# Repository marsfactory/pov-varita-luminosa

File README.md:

# pov-varita-luminosa
persistence of vision withs leds stick

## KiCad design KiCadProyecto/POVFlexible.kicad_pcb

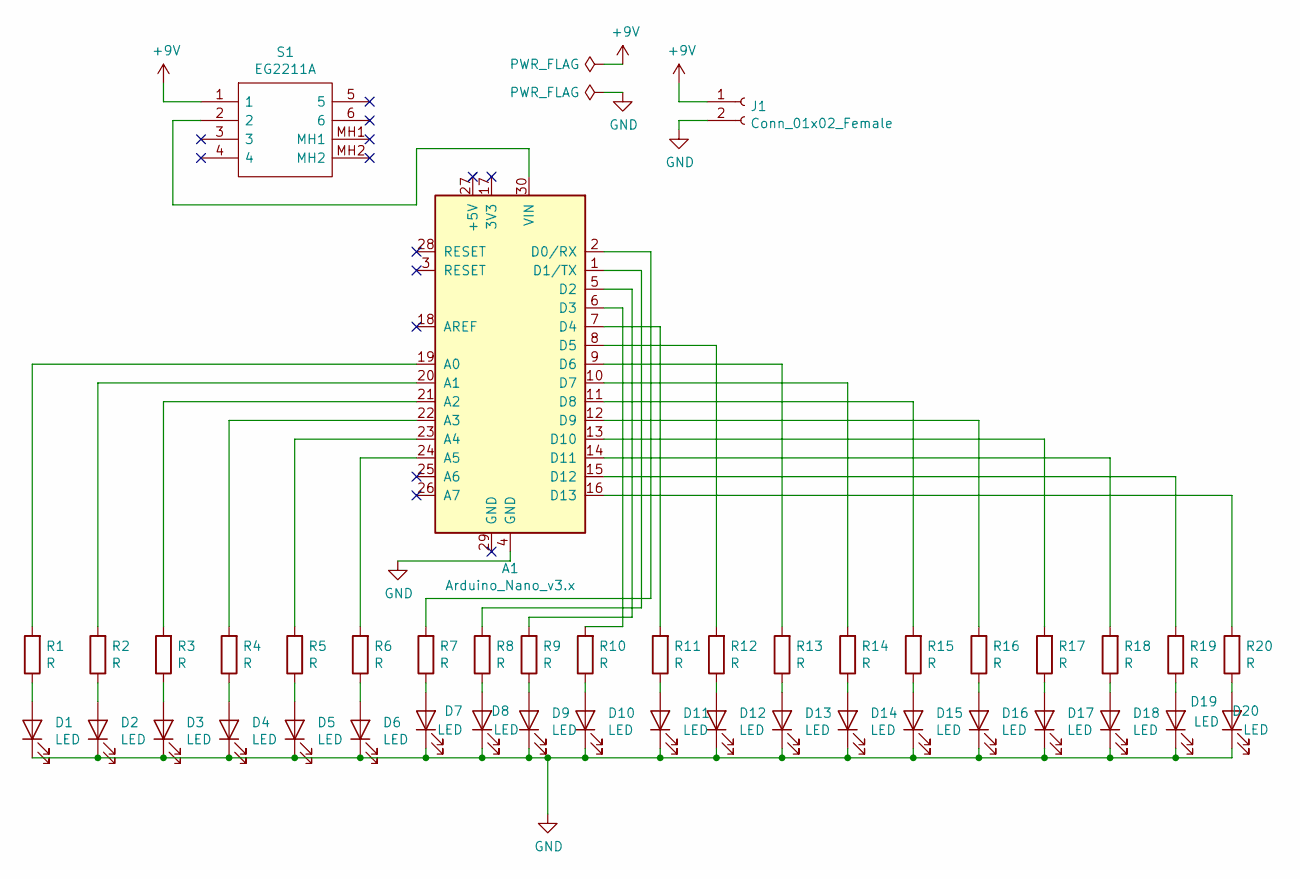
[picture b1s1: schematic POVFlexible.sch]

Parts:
A1: Arduino_Nano_v3.x; Arduino_Nano
D1, D2, D3, D4, D5, D6, D7, D8, D9, D10, D11, D12, D13, D14, D15, D16, D17, D18, D19, D20: LED; LED_D5.0mm
J1: Conn_01x02_Female; TerminalBlock_bornier-2_P5.08mm
R1, R2, R3, R4, R5, R6, R7, R8, R9, R10, R11, R12, R13, R14, R15, R16, R17, R18, R19, R20: R; R_Axial_DIN0207_L6.3mm_D2.5mm_P10.16mm_Horizontal
S1: EG2211A; Mouser Part Number 612-EG2211A

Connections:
GND: A1.4 (GND), D1.1 (K), D2.1 (K), D3.1 (K), D4.1 (K), D5.1 (K), D6.1 (K), D7.1 (K), D8.1 (K), D9.1 (K), D10.1 (K), D11.1 (K), D12.1 (K), D13.1 (K), D14.1 (K), D15.1 (K), D16.1 (K), D17.1 (K), D18.1 (K), D19.1 (K), D20.1 (K), J1.2; also elsewhere on the board
unnamed: A1.1 (D1/TX), R8.2
unnamed: A1.2 (D0/RX), R7.2
unnamed: A1.5 (D2), R9.2
unnamed: A1.6 (D3), R10.2
unnamed: A1.7 (D4), R11.2
unnamed: A1.8 (D5), R12.2
unnamed: A1.9 (D6), R13.2
unnamed: A1.10 (D7), R14.2
unnamed: A1.11 (D8), R15.2
unnamed: A1.12 (D9), R16.2
unnamed: A1.13 (D10), R17.2
unnamed: A1.14 (D11), R18.2
unnamed: A1.15 (D12), R19.2
unnamed: A1.16 (D13), R20.2
unnamed: A1.19 (A0), R1.2
unnamed: A1.20 (A1), R2.2
unnamed: A1.21 (A2), R3.2
unnamed: A1.22 (A3), R4.2
unnamed: A1.23 (A4), R5.2
unnamed: A1.24 (A5), R6.2
unnamed 30: A1.30 (VIN), S1.2; also elsewhere on the board
unnamed: D1.2 (A), R1.1
unnamed: D2.2 (A), R2.1
unnamed: D3.2 (A), R3.1
unnamed: D4.2 (A), R4.1
unnamed: D5.2 (A), R5.1
unnamed: D6.2 (A), R6.1
unnamed: D7.2 (A), R7.1
unnamed: D8.2 (A), R8.1
unnamed: D9.2 (A), R9.1
unnamed: D10.2 (A), R10.1
unnamed: D11.2 (A), R11.1
unnamed: D12.2 (A), R12.1
unnamed: D13.2 (A), R13.1
unnamed: D14.2 (A), R14.1
unnamed: D15.2 (A), R15.1
unnamed: D16.2 (A), R16.1
unnamed: D17.2 (A), R17.1
unnamed: D18.2 (A), R18.1
unnamed: D19.2 (A), R19.1
unnamed: D20.2 (A), R20.1
unnamed: J1.1, S1.1

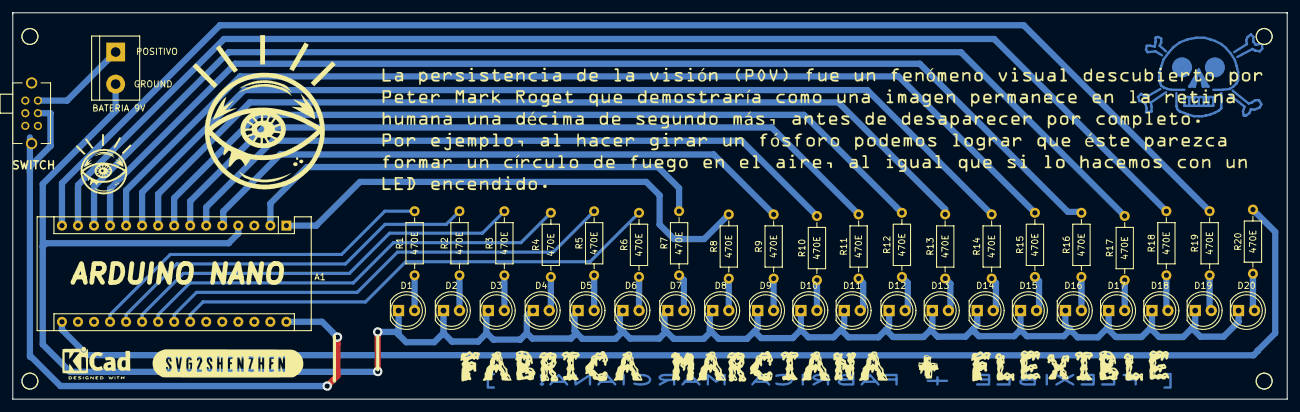
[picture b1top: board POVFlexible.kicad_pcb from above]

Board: 2 copper layers, 202.0 x 61.2 mm, 44 parts (0 on the bottom side), 43 nets.

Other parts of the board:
BATERIA 9V: Conn_01x02_Female; TerminalBlock_bornier-2_P5.08mm
Ref**: Val**; POV
SWITCH: EG2211A

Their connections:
+9V: BATERIA 9V.1, SWITCH.1
GND: BATERIA 9V.2; also elsewhere on the board
unnamed 30: SWITCH.2; also elsewhere on the board

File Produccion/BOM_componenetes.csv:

"Id";"Identificador";"Empaquetado";"Cantidad";"Identificación";"Suministrador y ref";
1;"REF**,REF**,REF**,REF**";"MountingHole_2.5mm";4;"MountingHole_2.5mm";;;
2;"Ref**";"POV";1;"Val**";;;
3;"REF**";"Symbol_Danger_CopperTop_Big";1;"Symbol_Danger_CopperTop_Big";;;
4;"BATERIA 9V";"TerminalBlock_bornier-2_P5.08mm";1;"Conn_01x02_Female";;;
5;"A1";"Arduino_Nano";1;"ARDUINO NANO";;;
6;"D1,D2,D3,D4,D5,D6,D7,D8,D9,D10,D11,D12,D13,D14,D15,D16,D17,D18,D19,D20";"LED_D5.0mm";20;"LED";;;
7;"R1,R2,R3,R4,R5,R6,R7,R8,R9,R10,R11,R12,R13,R14,R15,R16,R17,R18,R19,R20";"R_Axial_DIN0207_L6.3mm_D2.5mm_P10.16mm_Horizontal";20;"R";;;
8;"SWITCH";"EG2211A";1;"EG2211A";;;
